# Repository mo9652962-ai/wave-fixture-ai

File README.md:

<div align="center">

  # WAVE FIXTURE AI

  **Gerber 进 · 治具工程图出 · 21 项自动化 · 会听人话的 CAD 助手**

  **wave-fixture-ai 把波峰焊治具设计从手工描图变成一条命令：拖入 PCB Gerber 文件，自动生成沉板区、取手位、避位区、上锡区、压扣孔、定位销与治具外形，输出 DXF/STL/GLB；支持 3D 预览、元件干涉分析与自然语言参数调整（「避位区外扩1mm」等 29 参数确定性解析）。**

  <p>
    <a href="https://mo9652962-ai.github.io/wave-fixture-ai/"><strong>🌐 在线 3D 体验 / Live Demo</strong></a>
    ·
    <a href="README.en.md">English</a>
    ·
    <a href="#-在-ci-里用github-action">🤖 GitHub Action</a>
    ·
    <a href="llms.txt">📄 llms.txt (AI 直读)</a>
    ·
    <a href="VALIDATION.md">🧪 真实世界验证 (16 缺陷)</a>
    ·
    <a href="#-api-端点">🔌 API</a>
    ·
    <a href="LICENSE">MIT</a>
  </p>

  <p>

  </p>
</div>

<div align="center">
  
</div>

<div align="center">
  
  <p><sub>▲ 21 项自动化 · DXF / STL / GLB / CNC G 代码 / 生产报告交付 · Web 界面或命令行</sub></p>
</div>

<div align="center">

### ⭐ 如果 wave-fixture-ai 对你有帮助，点个 Star 就是最大的支持

</div>

## ✨ 21 项自动化

| 步骤 | 功能 | 状态 |
|:---|:---|:---|
| 1 | Gerber 上传识别（KiCad 10 兼容）| ✅ gerbonara + 正则回退 |
| 2 | 沉板区（外形外扩 0.2mm + R1.85 清角）| ✅ |
| 3 | 取手位（左右 20×40mm，重叠 1mm，R2 倒角）| ✅ |
| 4 | 压扣螺丝孔（Φ3.4，四角，距边 10mm）| ✅ |
| 5 | 定位销（DRL 钻孔内缩 0.1mm）| ✅ |
| 6 | 避位区（BOT+TOP 双面贴片包围 + 自动合并）| ✅ ESP32 板实测 |
| 7 | 上锡区（TOP 插件焊脚包围 + R2）| ✅ |
| 8 | 盖板弹力柱孔（丝印中心 Φ2.45）| ✅ |
| 9 | 治具外形（外扩整数化 + R5 + 轨道虚线 + 挡锡条）| ✅ |
| 10 | 输出治具 DXF（8 图层）| ✅ |
| 11 | **3D 预览**（STL/GLB 导出 + 浏览器旋转查看）| ✅ |
| 12 | **干涉分析**（元件 vs 治具：2D 覆盖 + 3D 布尔双层判定）| ✅ |
| 13 | **自然语言调整**（「避位区外扩1mm」等 29 参数）| ✅ |
| 14 | **DRC 生产安全门禁**（87 规则 · 四级严重度 · 每条带出处；未过 → 只出水印预览）| ✅ |
| 15 | **Golden Sample 回归验证**（IoU≥0.9 · Hausdorff≤0.5mm · 圆孔双向 best-match）| ✅ |
| 16 | **人工 Review 闭环**（缺数据/低置信度挂起 → 工程师确认 → SHA 绑定 + 审计日志）| ✅ |
| 17 | **定位销打分选点**（孔径窗口 / NPTH / 靠边权重 + 对角最大跨距）| ✅ |
| 18 | **内凹拐角狗骨头清角**（角平分线外移刀路 · 狗骨头/T-bone/角孔 · DXF「清角刀路」图层）| ✅ |
| 19 | **拼版阵列**（N×M 多片一治具 · 片间距挡锡墙 · 拼版后避位/上锡/销全量复制）| ✅ |
| 20 | **材料预设与成本估算**（Durostone/Ricocel/FR-4/铝 · 重量/材料费/工时费）| ✅ |
| 21 | **CNC G 代码直出 + 生产工单报告**（钻孔/挖腔/外形落料全工序 · .nc 交付 · Markdown 工单）| ✅ |

## 🚦 DRC 生产安全门禁（工业级核心）

治具出图前跑 87 条设计规则检查，**存在 blocking / error 时导出的 DXF 自动打水印**（`PREVIEW`），
禁止直接送 CNC 生产——这是"设计稿"与"生产件"之间的最后防线。

| 级别 | 含义 | 例 |
|:---|:---|:---|
| `blocking` | 几何无效，不能生产 | 沉板区超出治具外框、外形自交 |
| `error` | 工艺冲突，需修正 | 定位销落入避位区、压扣孔压到板边元件、治具超传送带极限（508×762mm）、治具短边超波峰焊轨距（默认 330mm）|
| `warning` | 建议优化 | 定位销/压扣少于 2 个、开口宽 <3.8mm（Macaos）、沉板壁厚 <1.5mm（APTPCB）、拼版间距 <3mm |
| `info` | 提示 | — |

每条规则都带 **出处**（竞品逆向框架 + Macaos / AGICORP / APTPCB / PCBSync / MB Manufacturing 的 DFM 指南），
不是拍脑袋的阈值。QA 闭环配套：

- **Golden Sample 回归**：`golden.py` 支持导出几何基准并断言 IoU ≥0.9、Hausdorff ≤0.5mm、圆孔位置/半径误差；
- **人工 Review**：缺层/低置信度**不自动猜**，挂起 mandatory review；工程师确认后写入
  `layer_mapping.json`（绑定 geometry SHA256——几何一变确认自动过期），pending 状态阻断生产放行。

## 🚀 快速开始（Web 界面，推荐）

```bash
# 安装（或 pip install -e . 后用 wave-fixture-ai 命令）
pip install -e .

wave-fixture-ai --port 8000
```

浏览器打开 **http://localhost:8000**，使用流程：

```
1. 拖入 Gerber 文件（.gbs/.gts/.gbl/.gtl/.gm1/.drl 等，可多选）
   建议包含：B_Mask + F_Mask + Edge_Cuts + B_Cu + F_Cu + .drl
2. 点「🚀 生成治具」→ 预览 2D + 下载 DXF/PNG
3. 点「🧊 生成 3D」→ 3D 旋转预览 + 下载 STL/GLB
4. （可选）干涉分析：再拖入 KiCad 工程文件 .kicad_pcb → 报告避位不足的元件
5. （可选）自然语言调整：输入如「避位区外扩1mm」→ 重新生成
```

## 🤖 在 CI 里用（GitHub Action）

在 PR 时自动为 PCB 生成波峰焊治具并跑 DRC 生产门禁——**可制造性问题在 PR 阶段暴露**，
防止把不可焊的板送去打样：

```yaml
name: drc
on: [pull_request, push]
jobs:
  fixture-drc:
    runs-on: ubuntu-latest
    permissions:
      contents: read
    steps:
      - uses: actions/checkout@v4
      - uses: mo9652962-ai/wave-fixture-ai@main
        with:
          gerber-dir: gerber/           # 你的 Gerber 产物目录
          severity-threshold: error     # error/blocking 问题让 CI 失败
```

产出：`fixture.dxf`（通过则为生产版，未过自动带 `PREVIEW` 水印）+ `drc-report.json`
自动上传为 `fixture-artifacts`。详见 [action.yml](action.yml)。本仓库 CI 每次 push 都在
用它审计自己的真实板用例（dogfood）。

## 🧩 MCP 服务（Claude Desktop / Cursor 等 AI 客户端）

内置 [Model Context Protocol](https://modelcontextprotocol.io) 服务（stdio 传输），让 AI 助手直接调用治具能力：
Gerber 解析、治具 DXF + DRC 门禁 + CNC G 代码生成、狗骨头清角、波峰导流倒角、热膨胀间隙校核、
量产报价、工艺窗口、预热曲线与锡渣/桥连预测，共 10 个工具（除治具生成会写入指定输出目录外，其余均为只读）。

```bash
pip install "git+https://github.com/mo9652962-ai/wave-fixture-ai"   # PyPI 下个版本起含 MCP；或仓库内 pip install -e .
wave-fixture-ai-mcp                # stdio 启动（一般由 AI 客户端自动拉起）
# 也可用 Docker：docker build -t wave-fixture-ai-mcp . && docker run -i --rm wave-fixture-ai-mcp
```

Claude Desktop（`claude_desktop_config.json`）或 Cursor（`~/.cursor/mcp.json`）配置示例：

```json
{
  "mcpServers": {
    "wave-fixture-ai": {
      "command": "wave-fixture-ai-mcp"
    }
  }
}
```

未全局安装时可用 uv 直接从仓库运行：`"command": "uvx"`，
`"args": ["--from", "git+https://github.com/mo9652962-ai/wave-fixture-ai", "wave-fixture-ai-mcp"]`。

## ⌨️ 命令行方式

```bash
# Phase 1（沉板区/取手位/压扣孔/定位销）
python fixture_phase1.py <gerber_dir> -o output/fixture.dxf

# Phase 2 完整（+避位区/上锡区/盖板/治具外形）
python fixture_phase2.py <gerber_dir> -o output/fixture-full.dxf

# 干涉分析（需 .kicad_pcb）
python -c "
from interference import parse_kicad_pcb, analyze_interference
comps = parse_kicad_pcb('board.kicad_pcb')
reports = analyze_interference('output/fixture.stl', comps)
"
```

## 🔌 API 端点

| 端点 | 功能 |
|:---|:---|
| `POST /api/generate` | 上传 Gerber → DXF + PNG |
| `POST /api/generate3d` | 上传 Gerber → 3D 治具（STL + GLB）|
| `POST /api/adjust` | 自然语言调整 → 重新生成 |
| `POST /api/interference` | 干涉分析（需含 .kicad_pcb）|
| `GET /dl/{file}` | 下载生成的文件 |

## 🔬 干涉分析说明

- 需要 **.kicad_pcb** 文件（Gerber 只有焊盘几何，无元件高度信息）
- 判定规则：元件盒在避位区覆盖 <85% 或 与治具 3D 重叠 >5mm³ → 报干涉
- 插件（PinHeader/Connector/USB 等）自动跳过（贯穿治具由「上锡区」处理）

## 💬 自然语言调整示例

```
避位区外扩1mm           → avoid_pad_extra: 0.3 → 1.3
沉板区外扩0.5mm          → sink_expand_mm: 0.2 → 0.7
盖板孔径改3mm            → cap_hole_r: 2.45 → 3.0
左右外扩加大20mm         → ext_left_right: 20.0 → 40.0
```

> 规则解析（确定性，不用 LLM）——工程参数调整要精确可复现。

## 🧰 技术栈

- **gerbonara** — Gerber/Excellon 解析（层自动识别 + KiCad10 G85 正则回退）
- **shapely** — 几何运算（外扩/倒角/凸包包围/坐标变换）
- **ezdxf** — DXF 输出
- **trimesh + manifold** — 3D 拉伸/布尔
- **fastapi + uvicorn** — Web 服务
- **three.js** — 前端 3D 渲染（ES module）

## 🏭 企业级交付（对标商业治具软件）

对标 Macaos Solder Pallet Designer（€1,500/年模块）的交付闭环，wave-fixture-ai 补齐四件企业级能力：

### 拼版阵列（Panelization）
小板一治具多片：界面输入 列×行 + 片间距，沉板/避位/上锡/定位销/狗骨头全量按阵列复制，
片间距挡锡墙默认 5mm（行业下限 3mm，低于阈值触发 DRC `PANEL_GAP_TOO_SMALL`）。

### 材料预设与成本估算
| 材料 | 密度 g/cm³ | 耐温 | 特性 | 适用 |
|:---|:---|:---|:---|:---|
| **Durostone 合成石** | 1.90 | 280°C | ESD 静电耗散 · 行业事实标准 | 双波/大批量 |
| Ricocel 合成石 | 1.85 | 280°C | Durostone 同类竞品 | 性价比路线 |
| 高 Tg FR-4 | 2.10 | 180°C | 低成本 | 打样/小批量 |
| 铝合金 6061 | 2.70 | 400°C | 高导热长寿命（需防挂锡） | 重载 |

自动输出：毛坯板厚吸附（向上取档）→ 重量估算 → 材料费 + 机加工费 → **报价参考**。
数据出处：Röchling 产品页 / Noves-China 板厚规格 / PCBSync 材料对比（见 `materials.py` 头注）。

### CNC G 代码直出（.nc）
DXF 之外直接交付机床可执行程序（RS-274，G21 mm / G90 绝对 / G54 / 换刀 M6 / M30 收尾）：

1. **钻孔组**：定位销孔按孔径分组自动换刀，分段啄钻；
2. **挖腔组**：避位/上锡/盖板孔（螺旋铣孔）/沉板槽（板厚+0.3mm）/取手位——行距光栅粗铣 + 每层轮廓精铣；
3. **外形落料**：刀具中心内缩一个刀径，切边落在治具边界。

进给/转速/层深/行距按材料预设给出安全默认值（合成石低进给高转速 + 强制吸尘提示），
程序头注释材料/板厚/刀具表，尾部附加工估时（本页示例真实板 39.2 min）。

### 批量作业（YAML 作业规格，KiBot 惯例）
```yaml
batch: "2026-W40 空调主板批"
defaults: { material: durostone, pallet_thickness: 10 }
jobs:
  - { name: aircon-main, gerber_dir: cases/case_002_aircon_kicad }
  - { name: stm32-carrier, gerber_dir: cases/case_003_stm32_4layer, panel_cols: 2 }
```
`python batch_run.py job.yaml` 一条命令产出整批 DXF/G 代码/工单 + 批次汇总，
单作业失败不中断批次（退出码可直接当 CI 门禁）。

### 波峰焊工艺窗口（作业指导书）
工单内置工艺参考窗口并做**材料-工艺交叉校验**：有铅 Sn63Pb37 锡炉 260±5°C/接触 2-5s、
无铅 SAC305 255-265°C/接触 4-8s（出处 Yint/Kester/Highqualitypcb，见 `process.py`）；
治具底面直接过波峰——材料耐温 <255°C（如高 Tg FR-4 180°C）触发 DRC `MATERIAL_TEMP_WINDOW` 警告。

### 生产工单报告（Markdown）
一次生成可归档/可传阅的 `*-report.md`：治具规格（含拼版）→ 材料与成本 → CNC 程序摘要 →
DRC 结论 → 干涉汇总 → 交付物清单，每项带数据出处。

> 真实板示例（case_003，2×1 拼版）：治具 130×105mm · Durostone 10mm · 毛坯 0.356kg ·
> 材料费 ¥149.5 + 加工费 ¥78.4 ≈ **¥227.9/套**

## 🧪 真实板验证（Golden Cases）

两类**真实生产板**的端到端回归基准（`cases/`）：

| Case | 来源 | 规格 | 覆盖 |
|:---|:---|:---|:---|
| `case_001_espmh` | EasyEDA 双排插针板（竞品 production sample + 人工基准） | 25.654×48.26mm · 31 钻孔 · 仅外形层 | 格式兼容（GBR/GER/GKO 三份等价外形）、微缺口闭合、无焊盘层时不凭空生成上锡区 |
| `case_002_aircon_kicad` | KiCad 空调板（含 B_Cu/B_Mask/Edge_Cuts 全层） | 100×80mm · 169 钻孔 · 5 种孔径 | KiCad 命名规范、大规模钻孔、真实避位/上锡区（20/24 个）、销径告警、3D 干涉判定 |
| `case_003_stm32_4layer` | **circuit-agent 生成的 4 层板**（跨仓/跨工具素材） | 37×37mm · 12 钻孔 · 含 3.2mm 安装孔 | **跨 AI-EDA 工具兼容性**、合格销径走打分正常路径、DRC 全绿正例 |

```bash
uv run pytest -q --cov --cov-fail-under=80    # 130 测试 · 覆盖率 84%（CI 棘轮 80）
uv run pytest tests/test_golden_case*.py -v    # 25 项真实板黄金断言
```

| 测试层 | 文件 | 覆盖内容 |
|:---|:---|:---|
| **真实板黄金**（25） | `test_golden_case00*.py` | 三来源板的几何精确性/设计规则/跨工具兼容 |
| **API 契约**（13） | `test_web_api.py` | 全部 7 个端点的字段契约、错误路径、产物可下载 |
| **解析健壮性**（8） | `test_drill_parsing.py` | METRIC/INCH 单位推断、英寸换算、G85 多孔、去重 |
| **3D 构建**（8） | `test_fixture_3d.py` | 布尔差集体积校验、失败告警、STL/GLB 导出 |
| **导出与编排**（5） | `test_phase1_export.py` | DXF 图层契约、孔为圆实体、无外形不产出 |
| **安全**（5） | `test_web_download_security.py` | 路径穿越拒绝、同名前缀目录、cwd 变化 |
| **模块单元**（66） | 其余 | DRC 规则/Golden/Review/销选点/几何/NL 调整 |

| 断言类别 | 内容 |
|:---|:---|
| 几何精确性 | 板尺寸/面积/钻孔数与人工基准**精确匹配**（偏差 0.000） |
| 设计规则 | 治具外形 =(板+2×外扩) 向上取整 5mm；压扣孔必在沉板区**外**；销径 ≥1.5mm |
| 工程约束 | 在传送带极限内；治具完整包含沉板区 |
| 门禁语义 | 无 blocking/error 才放行；无焊盘层不凭空生成上锡区 |

> 端到端跑通的过程修掉了 **11 个真实缺陷**（层名兼容 / overrides 语义 / 同层多文件 /
> 微缺口闭合 / 压扣孔位置 / 定位销未筛选 / 销径规则 / matplotlib 依赖 / 前端门禁未渲染 /
> **干涉判定 OR→AND 误报** / **板框 gr_line 解析**）——**单测 52 全绿时仍未被发现，
> 只有真实数据、真实浏览器与黄金对比能暴露**。方法论已沉淀为 `real-world-validation` 技能。
>
> 3D 干涉分析在真实板（36 元件）上的输出：报出的大体积元件（继电器 1886–2260mm³、
> 数码管 3163mm³）避位覆盖仅 0.04–0.60，是**真实设计缺陷**（大件落在避位区外会被治具压到）。

## 📄 许可证、安全与隐私 (License, Security & Privacy)

- **开源许可证**：[MIT License](LICENSE) © 2026 sora
- **安全政策**：[SECURITY.md](SECURITY.md)
- **隐私保护**：[PRIVACY.md](PRIVACY.md)（100% 本地运算、零外部遥测、工业图纸绝对保密）

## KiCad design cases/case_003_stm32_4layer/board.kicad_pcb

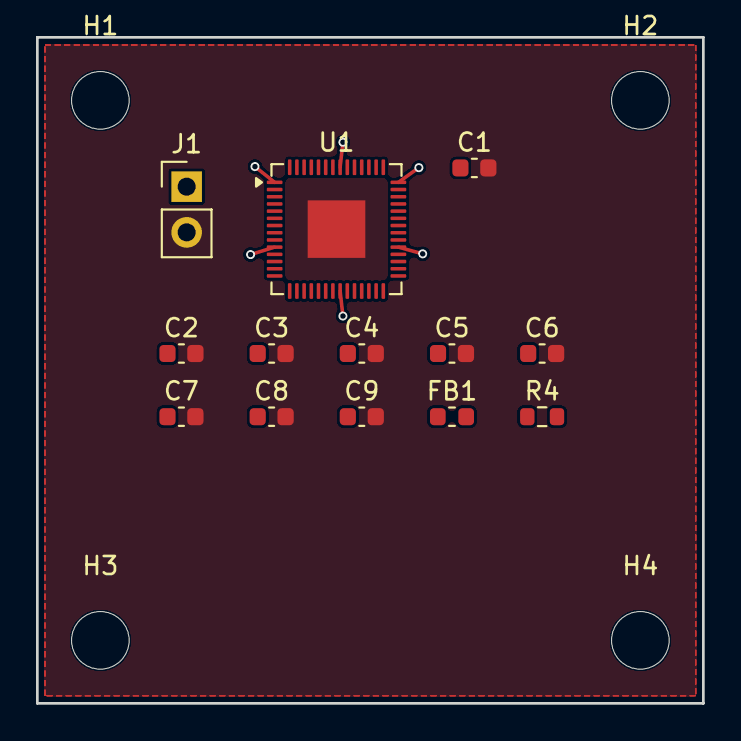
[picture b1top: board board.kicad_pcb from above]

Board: 4 copper layers, 37.0 x 37.0 mm, 17 parts (0 on the bottom side), 4 nets.

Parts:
C1, C2, C3, C4, C5, C7, C8, C9: 100nF; C_0603_1608Metric
C6: 10uF; C_0603_1608Metric
FB1: FERRITE_BEAD; L_0603_1608Metric
H1, H2, H3, H4: MountingHole_3.2mm_M3
J1: 3.3V power input; PinHeader_1x02_P2.54mm_Vertical
R4: 10k; R_0603_1608Metric
U1: RP2040; QFN-56-1EP_7x7mm_P0.4mm_EP3.2x3.2mm

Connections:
/+3.3V: C1.1, C2.1, C4.1, C5.1, C8.1, C9.1, FB1.1, J1.1, R4.2, U1.1, U1.10, U1.22, U1.33, U1.42, U1.49
/GND: C1.2, C2.2, C3.2, C4.2, C5.2, C6.2, C7.2, C8.2, C9.2, J1.2, U1.57
/RUN: C3.1, R4.1, U1.26
/VDDA_FILTERED: C6.1, C7.1, FB1.2, U1.43

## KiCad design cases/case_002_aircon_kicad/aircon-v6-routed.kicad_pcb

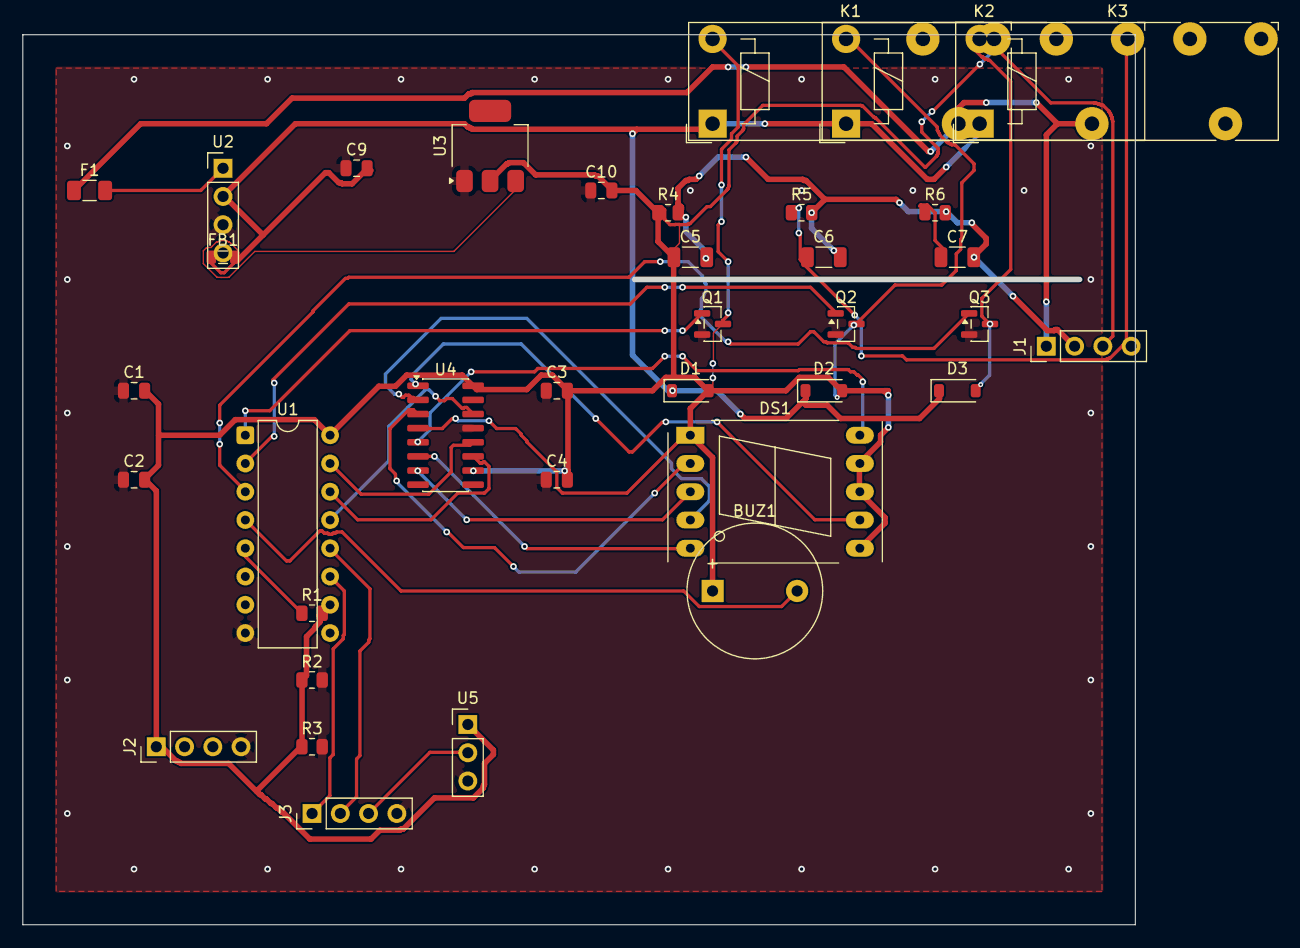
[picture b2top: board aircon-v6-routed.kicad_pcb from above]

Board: 2 copper layers, 100.0 x 80.0 mm, 36 parts (0 on the bottom side), 31 nets.

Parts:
BUZ1: Buzzer_12x9.5RM7.6
C1, C2, C3, C4, C9, C10: C_0805_2012Metric
C5, C6, C7: C_1206_3216Metric
D1, D2, D3: D_SOD-123
DS1: 7SegmentLED_LTS6760_LTS6780
F1: Fuse_1206_3216Metric
FB1: L_0805_2012Metric
J1, J2, J3: PinHeader_1x04_P2.54mm_Vertical
K1, K2, K3: Relay_1-Form-C_Schrack-RYII_RM3.2mm
Q1, Q2, Q3: SOT-23
R1, R2, R3, R4, R5, R6: R_0805_2012Metric
U1: DIP-16_W7.62mm
U2: PinHeader_1x04_P2.54mm_Vertical
U3: SOT-223
U4: SOIC-16_3.9x9.9mm_P1.27mm
U5: PinHeader_1x03_P2.54mm_Vertical

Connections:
AC_L: F1.1, J1.1, K1.11, K2.11, K3.11
AC_N: C5.2, C6.2, C7.2, J1.2, R4.2, R5.2, R6.2
AC_OUT1: C5.1, J1.3, K1.14, R4.1
AC_OUT2: C6.1, J1.4, K2.14, R5.1
AC_OUT3: C7.1, K3.14, R6.1
BUZZ: BUZ1.2, U1.4
GND: C1.1, C2.1, C3.1, C4.1, C9.1, C10.1, J2.4, J3.4, Q1.2, Q2.2, Q3.2, R2.2, R3.2, U1.8, U2.3, U2.4, U3.1, U4.8, U4.13, U5.3
IR: J3.3, U5.2
K1_DRV: Q1.1, U1.1
K2_DRV: Q2.1, U1.2
K3_DRV: Q3.1, U1.3
KEY1: J3.1, U1.11
KEY2: J3.2, U1.12
unnamed: F1.2, U2.1
unnamed: FB1.2, U3.3
unnamed: D1.2, K1.A2, Q1.3
unnamed: D2.2, K2.A2, Q2.3
unnamed: D3.2, K3.A2, Q3.3
unnamed: R1.1, U1.5
RCLK: U1.15, U4.12
SCK: U1.14, U4.11
SDI: U1.13, U4.14
SEG1: DS1.7, U4.1
SEG2: DS1.4, U4.2
SEG3: DS1.2, U4.3
SEG4: DS1.1, U4.4
SEG5: DS1.10, U4.5
SEG6: DS1.5, U4.6
SEG7: DS1.3, U4.7
V5: BUZ1.1, C1.2, C2.2, C3.2, C4.2, C10.2, DS1.6, DS1.8, DS1.9, J2.1, R1.2, R2.1, R3.1, U1.16, U3.2, U4.10, U4.16, U5.1
V12: C9.2, D1.1, D2.1, D3.1, FB1.1, K1.A1, K2.A1, K3.A1, U2.2
